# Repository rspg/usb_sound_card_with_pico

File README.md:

:point_right: [Japanese](./README_jp.md)

# USB Sound Card with Raspberry Pi Pico

## Introduction

This is a project for a USB sound card constructed with a Raspberry Pi Pico microcontroller board.  
Hardware schematics and firmware sourcecode are included.

## Features

- USB Audio Class 2.0 (Connected by USB 2.0 Full speed)
- 2ch Line in
- 2ch Line out
- 2ch SPDIF in
- 2ch SPDIF out
- 2ch Headphone out
- Maximum resolution is 24bit
- Maximum frequency is 96KHz

In/out USB data streams cannot activate simultaneously at 24-bit/96KHz due to a lack of transfer bandwidth.
"Line in" and "SPDIF in" are mixed into one buffer to save USB bandwidth. Each volume can be controlled via a generic USB driver. (Currently, it only supports Windows WinUSB.)

## Hardware

I used KiCad6 to design the schematics.  
If you want to view the schematics, Please download [KiCad 6 or later](https://www.kicad.org/).

The hardware design is simple and lacks ingenuity because I am not an electronics expert.
But I designed the schematics with the concept of separating modules by function to facilitate testing and adding other functions.  
Electronic components which are used are general and easily obtainable.   
The DAC uses PCM5102a and may be easily replaced with any of the PCM510x series. You can choose depending on their availability (although I have never tried this).

## Firmware 

The firmware is wrote by C and C++. 
SPDIF control does not use dedicated hardware and is implemented by the software using one of Pico's features called PIO. It allows running I/O independently of the main processor.
Similar to the schematics, the software is also organized by function. Each hardware function is represented as a class in the software.

To build the firmware, you should first install Pico's SDK and CMake.
For detailed instructions, please refer to the following resources.
- [Raspberry Pi Documentation The C/C++ SDK](https://www.raspberrypi.com/documentation/microcontrollers/c_sdk.html)  
- [CMake](https://cmake.org/)

Let's prepare a directory for Cmake setup.
> mkdir build  
> cd build  

For standard setup
> cmake ..  

With tracing log
> cmake .. -DLOG=1   

'LOG' is passed to tinyusb's debug level. That description is [here](https://docs.tinyusb.org/en/latest/reference/getting_started.html#log).

With profiling
> cmake .. -DPROFILE=1

To usb device control use TinyUSB. It is included in PicoSDK.
TinyUSB for Pico has a problem what memory deallocation of endpoint. Therefore, I prepared [a patch](patch/tinyusb-rp2040-allow-memory-preallocation.patch) for avoiding it. 
If you encounter to crashing the device in TinyUSB memory allocation,
It may resolve by applying [the patch](patch/tinyusb-rp2040-allow-memory-preallocation.patch) to TinyUSB.

## Debugging

The device outputs tracing log to serial port (CDC) owned myself. You can see the contents via serial monitor.   
And following commands are usable via serial monitor input.

> stats_on

Turn on the output of internal statistics every 0.5 seconds when the LOG is greater than 0.
 
> stats_off

Turn on output of internal stats.

> perf

Output measured performance statistics when profiling is enabled.

## Device unique request (Windows Only)
Unique requests to control internal behaviors from the host device have been implemented in the firmware.
If the host OS is Windows, the device requests the installation of the WinUSB driver to the OS through the Microsoft OS Descriptor description. This enables user-mode applications on the host to send requests to the device.

[control_uwp](control_uwp) is an application to controls the device volumes by using WinUSB via Windows Runtime.
To building requires [Visual Studio 2022 with C# UWP application development](https://visualstudio.microsoft.com/).

## References
- [Raspberry Pi Pico Datasheet](https://datasheets.raspberrypi.com/pico/pico-datasheet.pdf?_gl=1*lbhpfj*_ga*MjA5MDIxNzYzOC4xNjg0MzYzNDM5*_ga_22FD70LWDS*MTY5NjU4ODY5OS4zNS4xLjE2OTY1ODg5NTIuMC4wLjA.)  
- [RP2040 Datasheet](https://datasheets.raspberrypi.com/rp2040/rp2040-datasheet.pdf?_gl=1*1rlrh3d*_ga*MjA5MDIxNzYzOC4xNjg0MzYzNDM5*_ga_22FD70LWDS*MTY5NjU4ODY5OS4zNS4xLjE2OTY1ODg4OTYuMC4wLjA.)    
- [SPECIFICATION OF THE DIGITAL AUDIO INTERFACE (The AES/EBU interface)](https://tech.ebu.ch/docs/tech/tech3250.pdf)
- [Texas Instruments PCM510xA 2.1 VRMS, 112/106/100 dB Audio Stereo DAC with PLL and 32-bit, 384 kHz PCM Interface](https://www.ti.com/lit/ds/symlink/pcm5102a.pdf?ts=1696564046679&ref_url=https%253A%252F%252Fwww.ti.com%252Fproduct%252FPCM5102A)
- [Texas Instruments PCM1808 Single-Ended, Analog-Input 24-Bit, 96-kHz Stereo ADC](https://www.ti.com/jp/lit/ds/symlink/pcm1808.pdf?ts=1696503248668&ref_url=https%253A%252F%252Fwww.ti.com%252Fproduct%252Fja-jp%252FPCM1808)

## Disclaimer

I am not responsible and cannot guarantee any damage or injury that may occur if you decide to undertake this project.
Please keep in mind that this is a DIY project.

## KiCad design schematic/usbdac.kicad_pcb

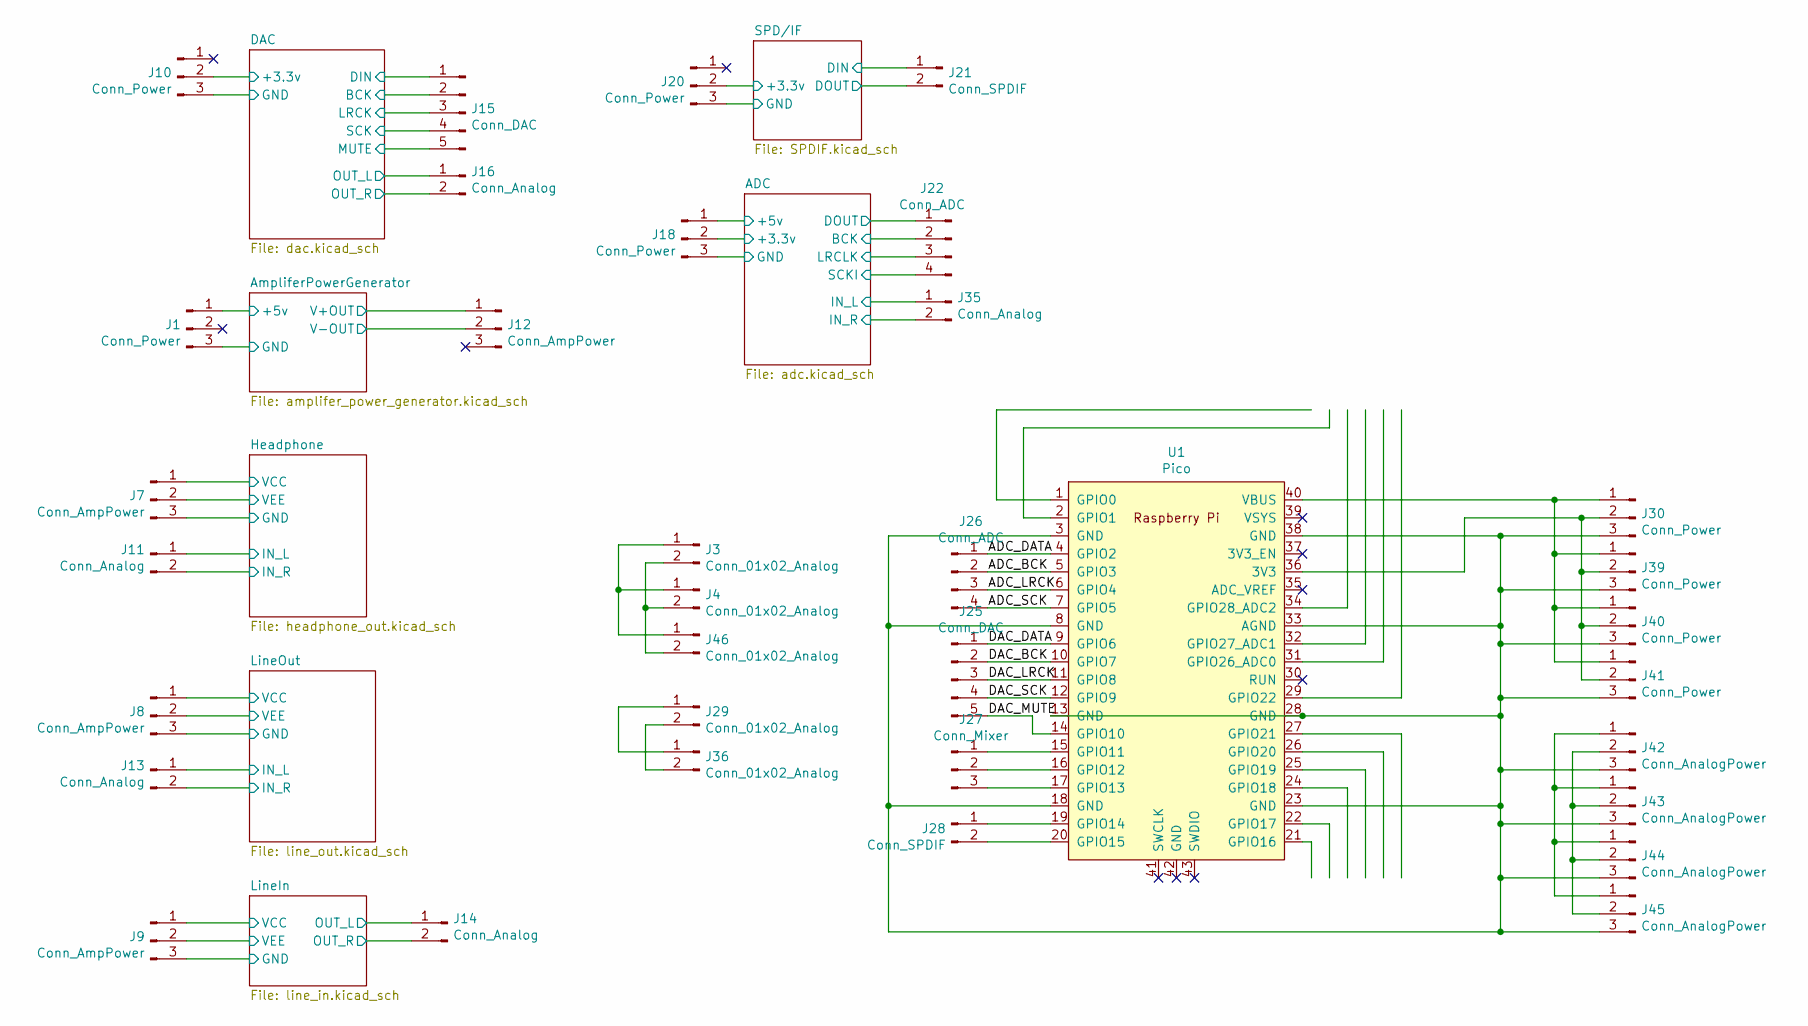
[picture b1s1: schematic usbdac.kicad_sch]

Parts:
J1, J10, J18, J20: Conn_Power; JST_ZH_S2B_ZR_1x03_P1.50mm_Horizontal_2layer
J3, J4, J29, J36, J46: Conn_01x02_Analog; PinHeader_1x02_P2.00mm_Vertical
J7, J8, J9, J12: Conn_AmpPower; JST_ZH_S2B_ZR_1x03_P1.50mm_Horizontal_2layer
J11, J13, J14, J16, J35: Conn_Analog; JST_ZH_S2B_ZR_1x02_P1.50mm_Horizontal_2layer
J15: Conn_DAC; JST_ZH_S2B_ZR_1x05_P1.50mm_Horizontal_2layer
J21: Conn_SPDIF; JST_ZH_S2B_ZR_1x02_P1.50mm_Horizontal_2layer
J22: Conn_ADC; JST_ZH_S2B_ZR_1x05_P1.50mm_Horizontal_2layer
J25: Conn_DAC; PinHeader_1x05_P2.00mm_Vertical
J26: Conn_ADC; PinHeader_1x04_P2.00mm_Vertical
J27: Conn_Mixer; PinHeader_1x03_P2.00mm_Vertical
J28: Conn_SPDIF; PinHeader_1x02_P2.00mm_Vertical
J30, J39, J40, J41: Conn_Power; PinHeader_1x03_P2.00mm_Vertical
J42, J43, J44, J45: Conn_AnalogPower; PinHeader_1x03_P2.00mm_Vertical
U1: Pico; RPi_Pico_WithPinHeader

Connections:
/ADC/+3.3v: J18.2; also elsewhere on the board
/ADC/+5v: J18.1; also elsewhere on the board
/ADC/BCK: J22.2; also elsewhere on the board
/ADC/DOUT: J22.1; also elsewhere on the board
/ADC/GND: J18.3; also elsewhere on the board
/ADC/IN_L: J35.1; also elsewhere on the board
/ADC/IN_R: J35.2; also elsewhere on the board
/ADC/LRCLK: J22.3; also elsewhere on the board
/ADC/SCKI: J22.4; also elsewhere on the board
/ADC_BCK: J26.2, U1.5 (GPIO3)
/ADC_DATA: J26.1, U1.4 (GPIO2)
/ADC_LRCK: J26.3, U1.6 (GPIO4)
/ADC_SCK: J26.4, U1.7 (GPIO5)
/AmpliferPowerGenerator/+5v: J1.1, J12.1; also elsewhere on the board
/AmpliferPowerGenerator/GND: J1.3; also elsewhere on the board
/AmpliferPowerGenerator/V-OUT: J12.2; also elsewhere on the board
/DAC/+3.3v: J10.2; also elsewhere on the board
/DAC/BCK: J15.2; also elsewhere on the board
/DAC/DIN: J15.1; also elsewhere on the board
/DAC/GND: J10.3; also elsewhere on the board
/DAC/LRCK: J15.3; also elsewhere on the board
/DAC/MUTE: J15.5; also elsewhere on the board
/DAC/OUT_L: J16.1; also elsewhere on the board
/DAC/OUT_R: J16.2; also elsewhere on the board
/DAC/SCK: J15.4; also elsewhere on the board
/DAC_BCK: J25.2, U1.10 (GPIO7)
/DAC_DATA: J25.1, U1.9 (GPIO6)
/DAC_LRCK: J25.3, U1.11 (GPIO8)
/DAC_MUTE: J25.5, U1.14 (GPIO10)
/DAC_SCK: J25.4, U1.12 (GPIO9)
/Headphone/GND: J7.3; also elsewhere on the board
/Headphone/IN_L: J11.1; also elsewhere on the board
/Headphone/IN_R: J11.2; also elsewhere on the board
/Headphone/VCC: J7.1; also elsewhere on the board
/Headphone/VEE: J7.2; also elsewhere on the board
/LineIn/GND: J9.3; also elsewhere on the board
/LineIn/OUT_L: J14.1; also elsewhere on the board
/LineIn/OUT_R: J14.2; also elsewhere on the board
/LineIn/VCC: J9.1; also elsewhere on the board
/LineIn/VEE: J9.2; also elsewhere on the board
/LineOut/GND: J8.3; also elsewhere on the board
/LineOut/IN_L: J13.1; also elsewhere on the board
/LineOut/IN_R: J13.2; also elsewhere on the board
/LineOut/VCC: J8.1; also elsewhere on the board
/LineOut/VEE: J8.2; also elsewhere on the board
/SPD/IF/+3.3v: J20.2; also elsewhere on the board
/SPD/IF/DIN: J21.1; also elsewhere on the board
/SPD/IF/DOUT: J21.2; also elsewhere on the board
/SPD/IF/GND: J20.3; also elsewhere on the board
unnamed: J3.1, J4.1, J46.1
unnamed: J3.2, J4.2, J46.2
unnamed: J27.1, U1.15 (GPIO11)
unnamed: J27.2, U1.16 (GPIO12)
unnamed: J27.3, U1.17 (GPIO13)
unnamed: J28.1, U1.19 (GPIO14)
unnamed: J28.2, U1.20 (GPIO15)
unnamed: J29.1, J36.1
unnamed: J29.2, J36.2
unnamed: J30.1, J39.1, J40.1, J41.1, U1.40 (VBUS)
unnamed: J30.2, J39.2, J40.2, J41.2, U1.36 (3V3)
unnamed: J30.3, J39.3, J40.3, J41.3, J42.3, J43.3, J44.3, J45.3, U1.3 (GND), U1.8 (GND), U1.13 (GND), U1.18 (GND), U1.23 (GND), U1.28 (GND), U1.33 (AGND), U1.38 (GND)
unnamed: J42.1, J43.1, J44.1, J45.1
unnamed: J42.2, J43.2, J44.2, J45.2

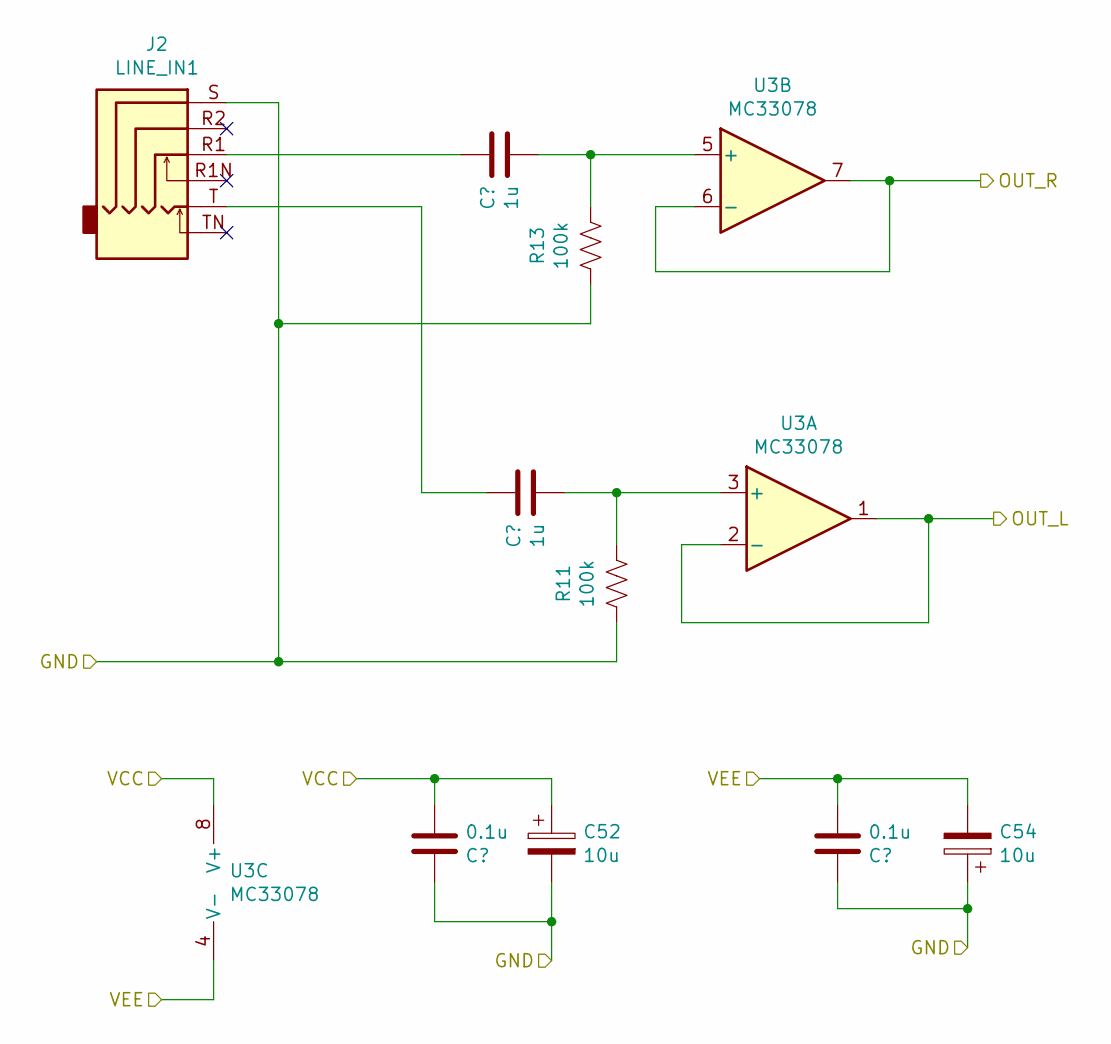
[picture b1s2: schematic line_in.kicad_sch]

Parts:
C26, C28: 1u; C_0603_1608Metric
C51, C53: 0.1u; C_0603_1608Metric
C52, C54: 10u; CP_Elec_4x3.9
J2: LINE_IN1; Jack_3.5mm_PJ31060-I_Horizontal
R11, R13: 100k; R_0603_1608Metric
U3: MC33078; SO-8_3.9x4.9mm_P1.27mm

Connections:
/LineIn/GND: C51.2, C52.2, C53.2, C54.1, J2.S, R11.1, R13.1; also elsewhere on the board
/LineIn/OUT_L: U3.1, U3.2 (-); also elsewhere on the board
/LineIn/OUT_R: U3.6 (-), U3.7; also elsewhere on the board
/LineIn/VCC: C51.1, C52.1, U3.8 (V+); also elsewhere on the board
/LineIn/VEE: C53.1, C54.2, U3.4 (V-); also elsewhere on the board
unnamed: C26.2, J2.T
unnamed: C28.2, J2.R1
unnamed: C26.1, R11.2, U3.3 (+)
unnamed: C28.1, R13.2, U3.5 (+)

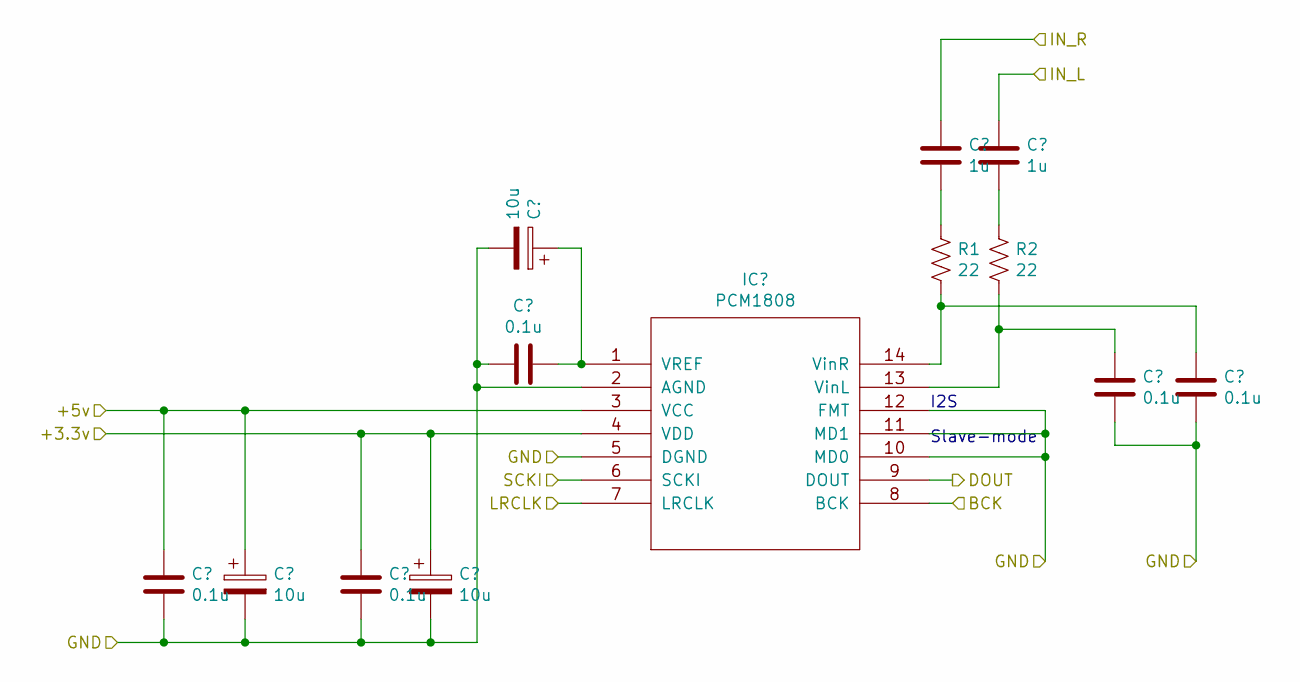
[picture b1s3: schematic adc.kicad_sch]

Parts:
C11, C14, C34, C36, C39: 0.1u; C_0603_1608Metric
C35, C37, C38: 10u; C_0603_1608Metric
C40, C41: 1u; C_0603_1608Metric
IC1: PCM1808; TI_R-PDSO-G14
R1, R2: 22; R_0603_1608Metric

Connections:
/ADC/+3.3v: C36.2, C37.1, IC1.4 (VDD); also elsewhere on the board
/ADC/+5v: C34.2, C35.1, IC1.3 (VCC); also elsewhere on the board
/ADC/BCK: IC1.8 (BCK); also elsewhere on the board
/ADC/DOUT: IC1.9 (DOUT); also elsewhere on the board
/ADC/GND: C11.1, C14.1, C34.1, C35.2, C36.1, C37.2, C38.2, C39.1, IC1.2 (AGND), IC1.5 (DGND), IC1.10 (MD0), IC1.11 (MD1), IC1.12 (FMT); also elsewhere on the board
/ADC/IN_L: C41.2; also elsewhere on the board
/ADC/IN_R: C40.2; also elsewhere on the board
/ADC/LRCLK: IC1.7 (LRCLK); also elsewhere on the board
/ADC/SCKI: IC1.6 (SCKI); also elsewhere on the board
unnamed: C40.1, R1.1
unnamed: C41.1, R2.1
unnamed: C38.1, C39.2, IC1.1 (VREF)
unnamed: C11.2, IC1.13 (VinL), R2.2
unnamed: C14.2, IC1.14 (VinR), R1.2

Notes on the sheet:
Slave-mode
I2S

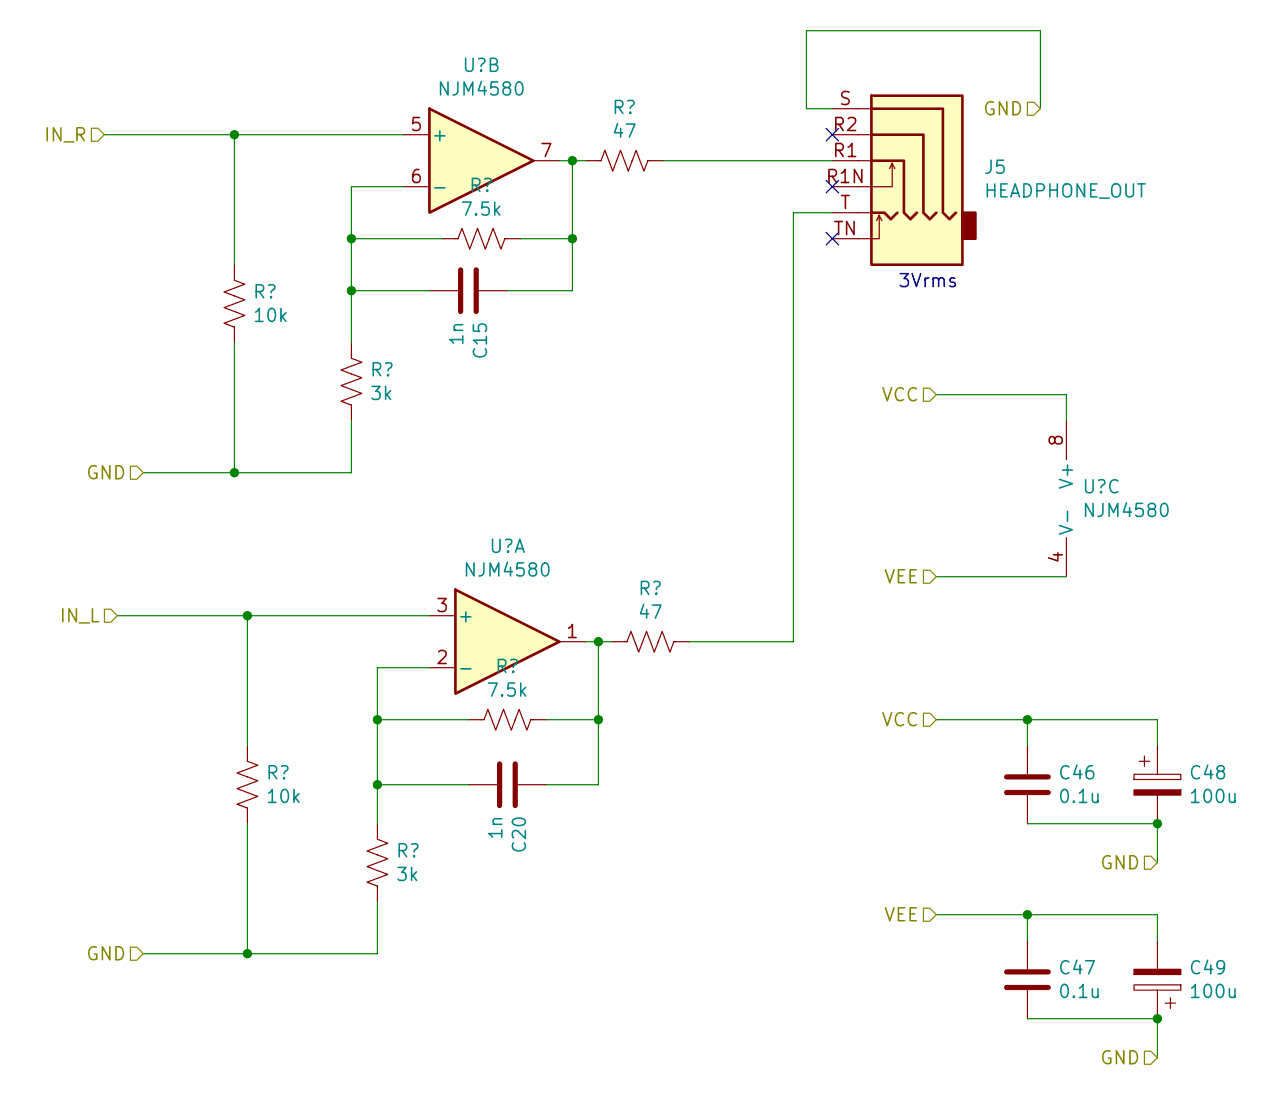
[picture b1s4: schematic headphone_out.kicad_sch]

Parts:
C15, C20: 1n; C_0603_1608Metric
C46, C47: 0.1u; C_0603_1608Metric
C48, C49: 100u; CP_Elec_6.3x5.4
J5: HEADPHONE_OUT; Jack_3.5mm_PJ31060-I_Horizontal
R3, R4: 10k; R_0603_1608Metric
R45, R46: 3k; R_0603_1608Metric
R47, R48: 7.5k; R_0603_1608Metric
R49, R50: 47; R_0603_1608Metric
U16: NJM4580; DIP-8_W7.62mm_SMDSocket_SmallPads

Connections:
/Headphone/GND: C46.2, C47.2, C48.2, C49.1, J5.S, R3.2, R4.2, R45.2, R46.2; also elsewhere on the board
/Headphone/IN_L: R4.1, U16.3 (+); also elsewhere on the board
/Headphone/IN_R: R3.1, U16.5 (+); also elsewhere on the board
/Headphone/VCC: C46.1, C48.1, U16.8 (V+); also elsewhere on the board
/Headphone/VEE: C47.1, C49.2, U16.4 (V-); also elsewhere on the board
unnamed: C15.1, R48.2, R50.1, U16.7
unnamed: C20.1, R47.2, R49.1, U16.1
unnamed: J5.R1, R50.2
unnamed: J5.T, R49.2
unnamed: C20.2, R45.1, R47.1, U16.2 (-)
unnamed: C15.2, R46.1, R48.1, U16.6 (-)

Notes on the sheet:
3Vrms

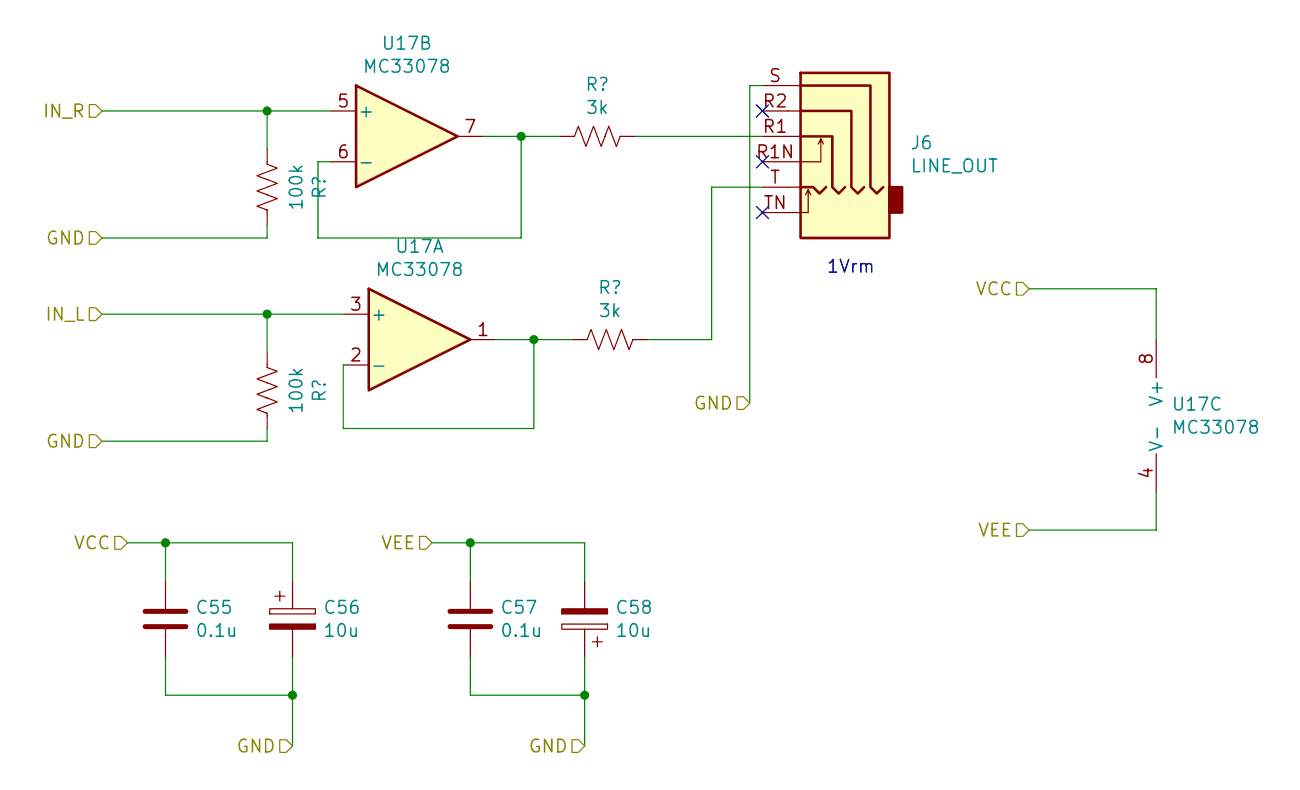
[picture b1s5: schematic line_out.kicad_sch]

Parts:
C55, C57: 0.1u; C_0603_1608Metric
C56, C58: 10u; CP_Elec_4x3.9
J6: LINE_OUT; Jack_3.5mm_PJ31060-I_Horizontal
R5, R44: 100k; R_0603_1608Metric
R51, R52: 3k; R_0603_1608Metric
U17: MC33078; SO-8_3.9x4.9mm_P1.27mm

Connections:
/LineOut/GND: C55.2, C56.2, C57.2, C58.1, J6.S, R5.2, R44.2; also elsewhere on the board
/LineOut/IN_L: R44.1, U17.3 (+); also elsewhere on the board
/LineOut/IN_R: R5.1, U17.5 (+); also elsewhere on the board
/LineOut/VCC: C55.1, C56.1, U17.8 (V+); also elsewhere on the board
/LineOut/VEE: C57.1, C58.2, U17.4 (V-); also elsewhere on the board
unnamed: J6.R1, R52.2
unnamed: J6.T, R51.2
unnamed: R51.1, U17.1, U17.2 (-)
unnamed: R52.1, U17.6 (-), U17.7

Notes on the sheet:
1Vrm

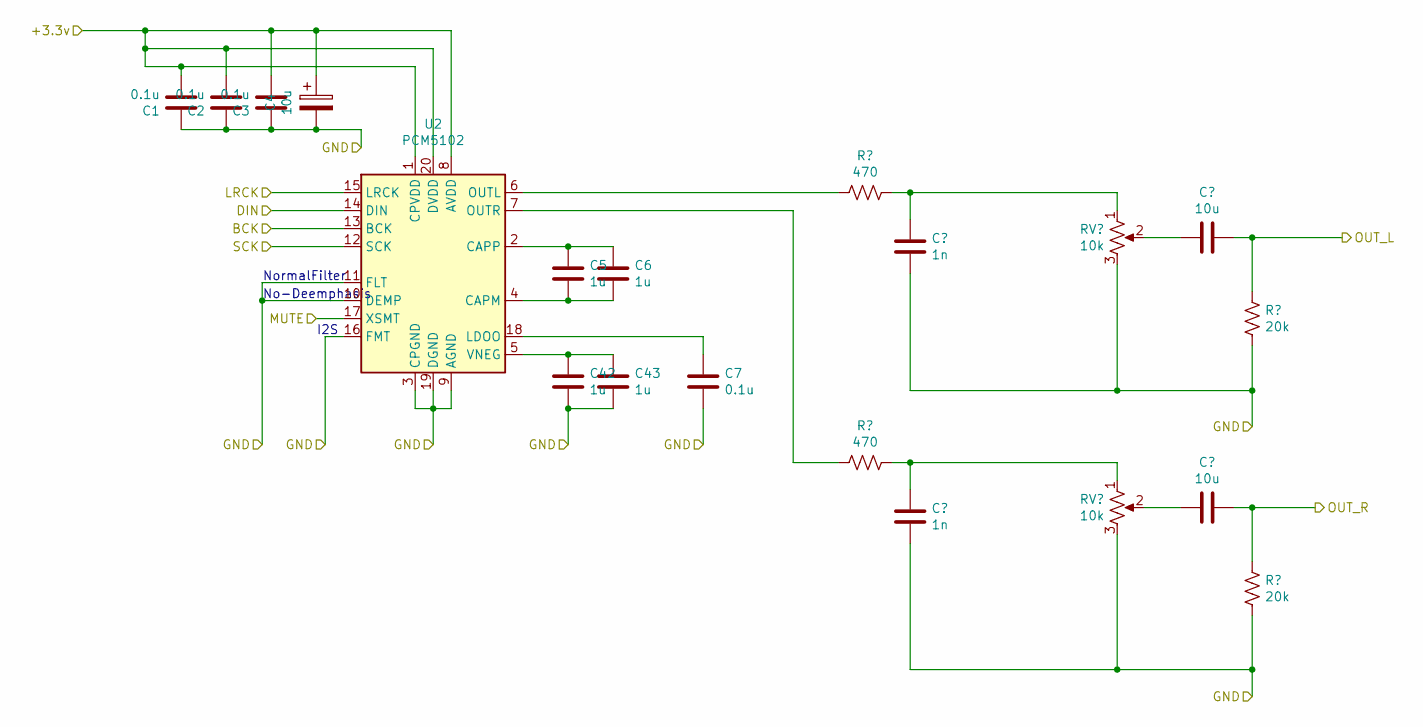
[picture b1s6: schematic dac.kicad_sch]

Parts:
C1, C2, C3, C7: 0.1u; C_0603_1608Metric
C4, C10, C23: 10u; C_0603_1608Metric
C5, C6, C42, C43: 1u; C_0603_1608Metric
C8, C9: 1n; C_0603_1608Metric
R6, R7: 470; R_0603_1608Metric
R8, R9: 20k; R_0603_1608Metric
RV1, RV2: 10k; Potentiometer_Bourns_TC33X_Vertical
U2: PCM5102; TSSOP-20_4.4x6.5mm_P0.65mm

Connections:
/DAC/+3.3v: C1.2, C2.2, C3.2, C4.1, U2.1 (CPVDD), U2.8 (AVDD), U2.20 (DVDD); also elsewhere on the board
/DAC/BCK: U2.13 (BCK); also elsewhere on the board
/DAC/DIN: U2.14 (DIN); also elsewhere on the board
/DAC/GND: C1.1, C2.1, C3.1, C4.2, C7.2, C8.2, C9.2, C42.2, C43.2, R8.2, R9.2, RV1.3, RV2.3, U2.3 (CPGND), U2.9 (AGND), U2.10 (DEMP), U2.11 (FLT), U2.16 (FMT), U2.19 (DGND); also elsewhere on the board
/DAC/LRCK: U2.15 (LRCK); also elsewhere on the board
/DAC/MUTE: U2.17 (XSMT); also elsewhere on the board
/DAC/OUT_L: C10.2, R8.1; also elsewhere on the board
/DAC/OUT_R: C23.2, R9.1; also elsewhere on the board
/DAC/SCK: U2.12 (SCK); also elsewhere on the board
unnamed: C8.1, R6.2, RV1.1
unnamed: C9.1, R7.2, RV2.1
unnamed: C10.1, RV1.2
unnamed: C23.1, RV2.2
unnamed: C5.2, C6.2, U2.4 (CAPM)
unnamed: C5.1, C6.1, U2.2 (CAPP)
unnamed: C7.1, U2.18 (LDOO)
unnamed: R6.1, U2.6 (OUTL)
unnamed: R7.1, U2.7 (OUTR)
unnamed: C42.1, C43.1, U2.5 (VNEG)

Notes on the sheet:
I2S
No-Deemphasis
NormalFilter

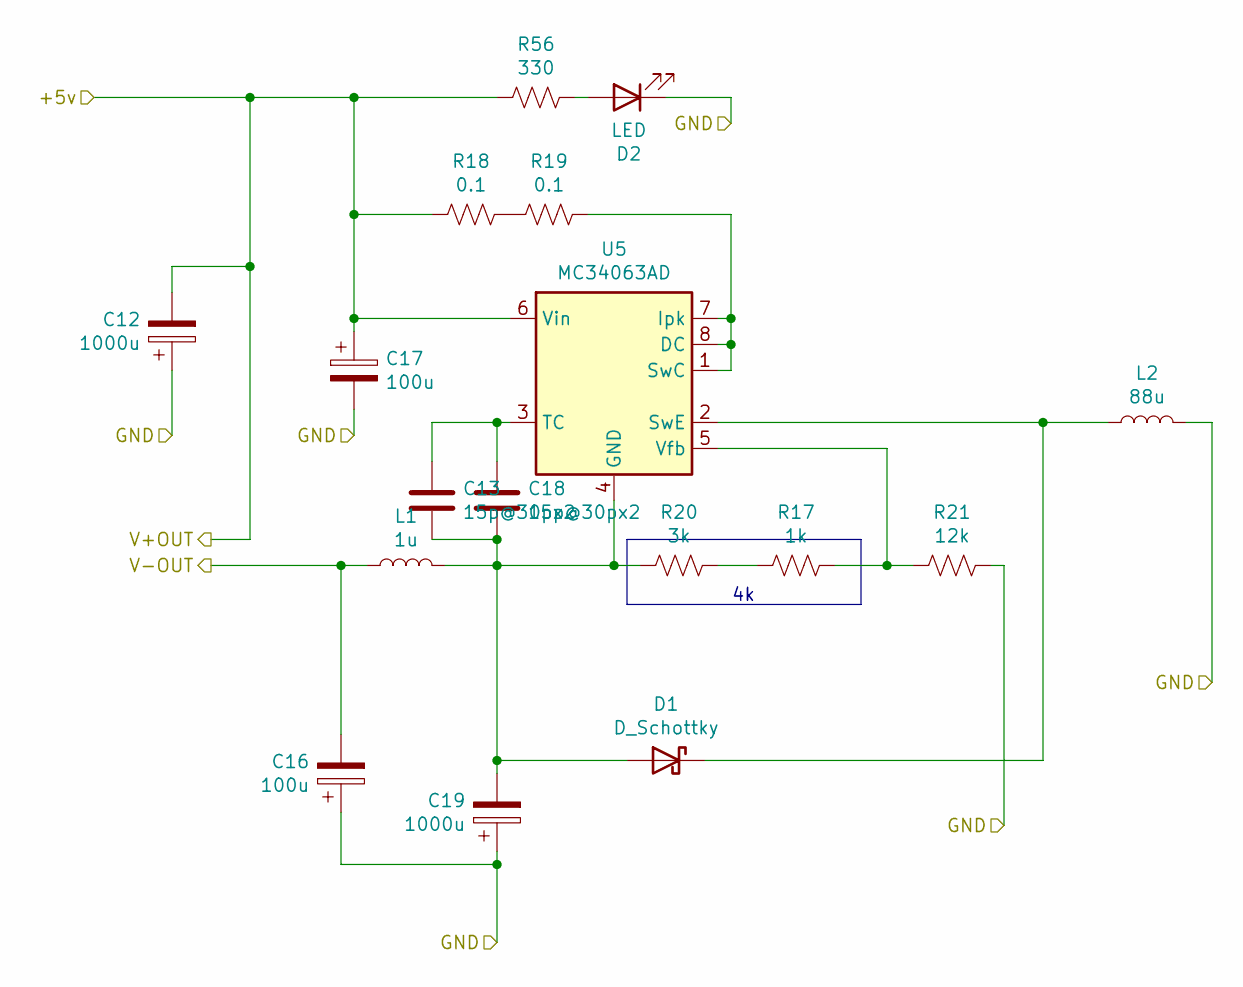
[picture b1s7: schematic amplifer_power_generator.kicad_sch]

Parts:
C12, C19: 1000u; CP_Elec_10x10
C13, C18: 15p@30px2; C_0603_1608Metric
C16, C17: 100u; CP_Elec_6.3x5.4
D1: D_Schottky; CUS01
D2: LED; LED_0805_2012Metric
L1: 1u; L_0603_1608Metric
L2: 88u; L_Taiyo-Yuden_NR-10050_9.8x10.0mm
R17: 1k; R_0603_1608Metric
R18, R19: 0.1; R_1210_3225Metric
R20: 3k; R_0603_1608Metric
R21: 12k; R_0603_1608Metric
R56: 330; R_0603_1608Metric
U5: MC34063AD; SOIC-8_3.9x4.9mm_P1.27mm

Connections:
/AmpliferPowerGenerator/+5v: C12.2, C17.1, R18.1, R56.1, U5.6 (Vin); also elsewhere on the board
/AmpliferPowerGenerator/GND: C12.1, C16.1, C17.2, C19.1, D2.1 (K), L2.2, R21.2; also elsewhere on the board
/AmpliferPowerGenerator/V-OUT: C16.2, L1.1; also elsewhere on the board
unnamed: C13.2, C18.2, C19.2, D1.2 (A), L1.2, R20.1, U5.4 (GND)
unnamed: D1.1 (K), L2.1, U5.2 (SwE)
unnamed: D2.2 (A), R56.2
unnamed: R17.1, R20.2
unnamed: R18.2, R19.1
unnamed: R19.2, U5.1 (SwC), U5.7 (Ipk), U5.8 (DC)
unnamed: C13.1, C18.1, U5.3 (TC)
unnamed: R17.2, R21.1, U5.5 (Vfb)

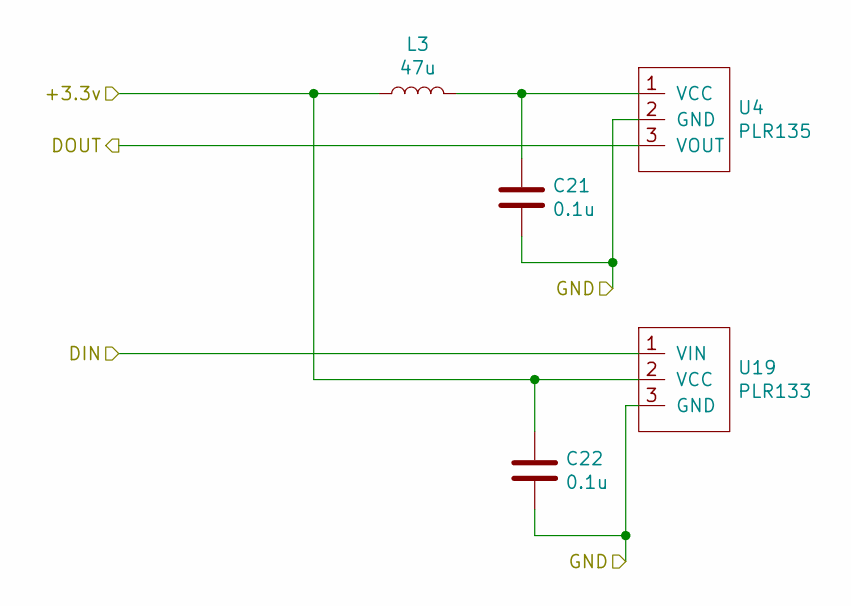
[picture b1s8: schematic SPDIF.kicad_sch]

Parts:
C21, C22: 0.1u; C_0603_1608Metric
L3: 47u; A915AY-100M
U4: PLR135; PLR133-135
U19: PLR133; PLR133-135

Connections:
/SPD/IF/+3.3v: C22.1, L3.1, U19.2 (VCC); also elsewhere on the board
/SPD/IF/DIN: U19.1 (VIN); also elsewhere on the board
/SPD/IF/DOUT: U4.3 (VOUT); also elsewhere on the board
/SPD/IF/GND: C21.2, C22.2, U4.2 (GND), U19.3 (GND); also elsewhere on the board
unnamed: C21.1, L3.2, U4.1 (VCC)

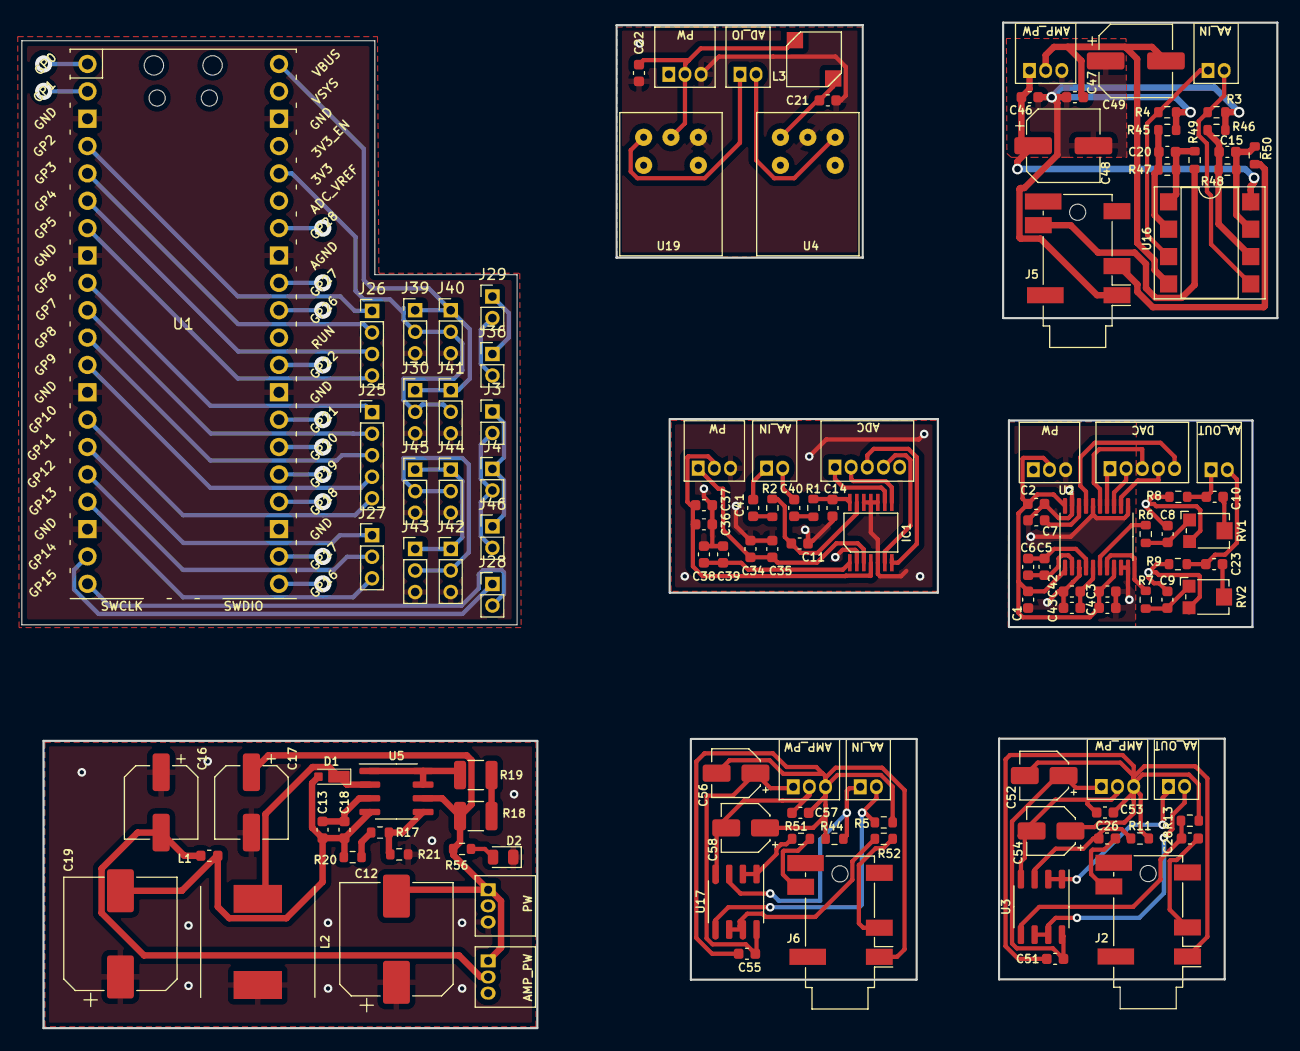
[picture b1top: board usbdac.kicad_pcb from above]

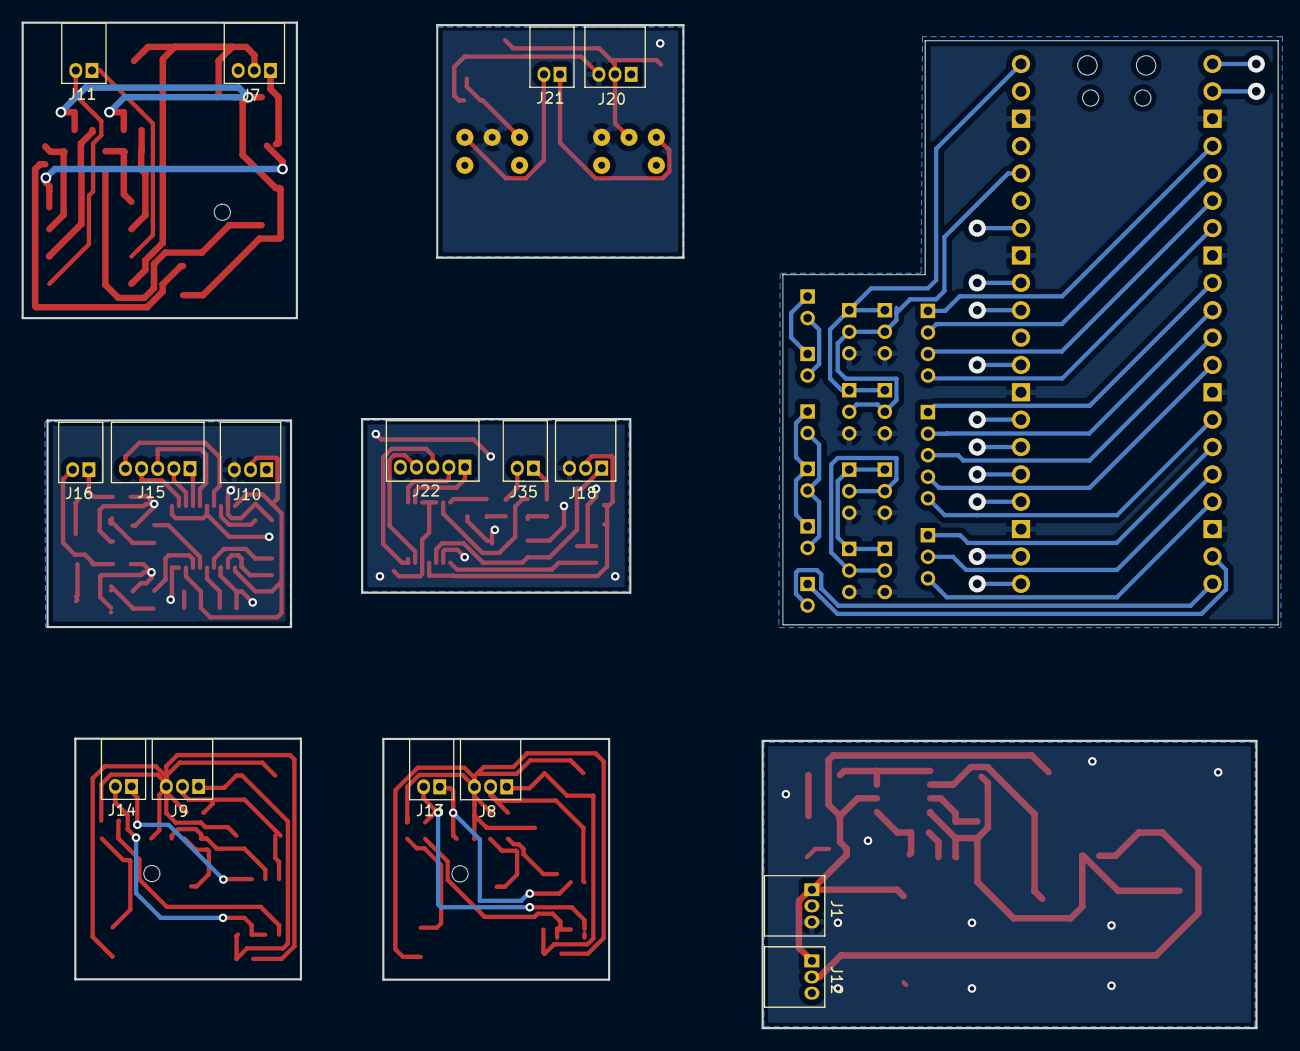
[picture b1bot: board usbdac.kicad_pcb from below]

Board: 2 copper layers, 116.5 x 93.3 mm, 125 parts (16 on the bottom side), 101 nets.

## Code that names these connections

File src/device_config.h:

#pragma once

#include <stdint.h>
#include "usb_config.h"

#define SPDIF_OUTPUT_ENABLE     1
#define DAC_OUTPUT_ENABLE       1
#define SPDIF_INPUT_ENABLE      1
#define ADC_INPUT_ENABLE        1
#define MIXING_INPUT_TO_OUTPUT_ENABLE  1

constexpr uint8_t  device_output_channels = 2;
constexpr uint8_t  device_input_channels = 2;
constexpr uint8_t  max_resolution_bits = 24;
constexpr uint32_t max_sampling_frequency = 96000;
constexpr uint32_t max_byte_per_sample = max_resolution_bits*device_output_channels/8; // 24bit 2ch
constexpr size_t   max_output_samples_1ms = max_sampling_frequency*device_output_channels/1000;
constexpr size_t   max_input_samples_1ms = max_sampling_frequency*device_input_channels/1000;


namespace gpio_assign
{
    constexpr uint spdif_tx = 14;
    constexpr uint spdif_rx = 15;

    constexpr uint dac_data = 6;
    constexpr uint dac_bck_lrck = 7;
    constexpr uint dac_sck = 9;
    constexpr uint dac_mute = 10;

    constexpr uint adc_data = 2;
    constexpr uint adc_bck_lrck = 3;
    constexpr uint adc_sck = 5;
}

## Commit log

2023-10-05 first commiting
2023-10-06 match readme jp to english
2023-10-06 add references
2023-10-10 preallocate audio fb memory
2023-10-10 fix openocd path of task
2023-10-13 fixed the english readme contents powerd by ChatGPT
2023-10-26 fix PID in control_uwp
